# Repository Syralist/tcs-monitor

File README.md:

# tcs-monitor
ein Bus-Monitor für TCS Klingelanlagen

# credits
Version3 basiert auf https://github.com/atc1441/TCSintercomArduino

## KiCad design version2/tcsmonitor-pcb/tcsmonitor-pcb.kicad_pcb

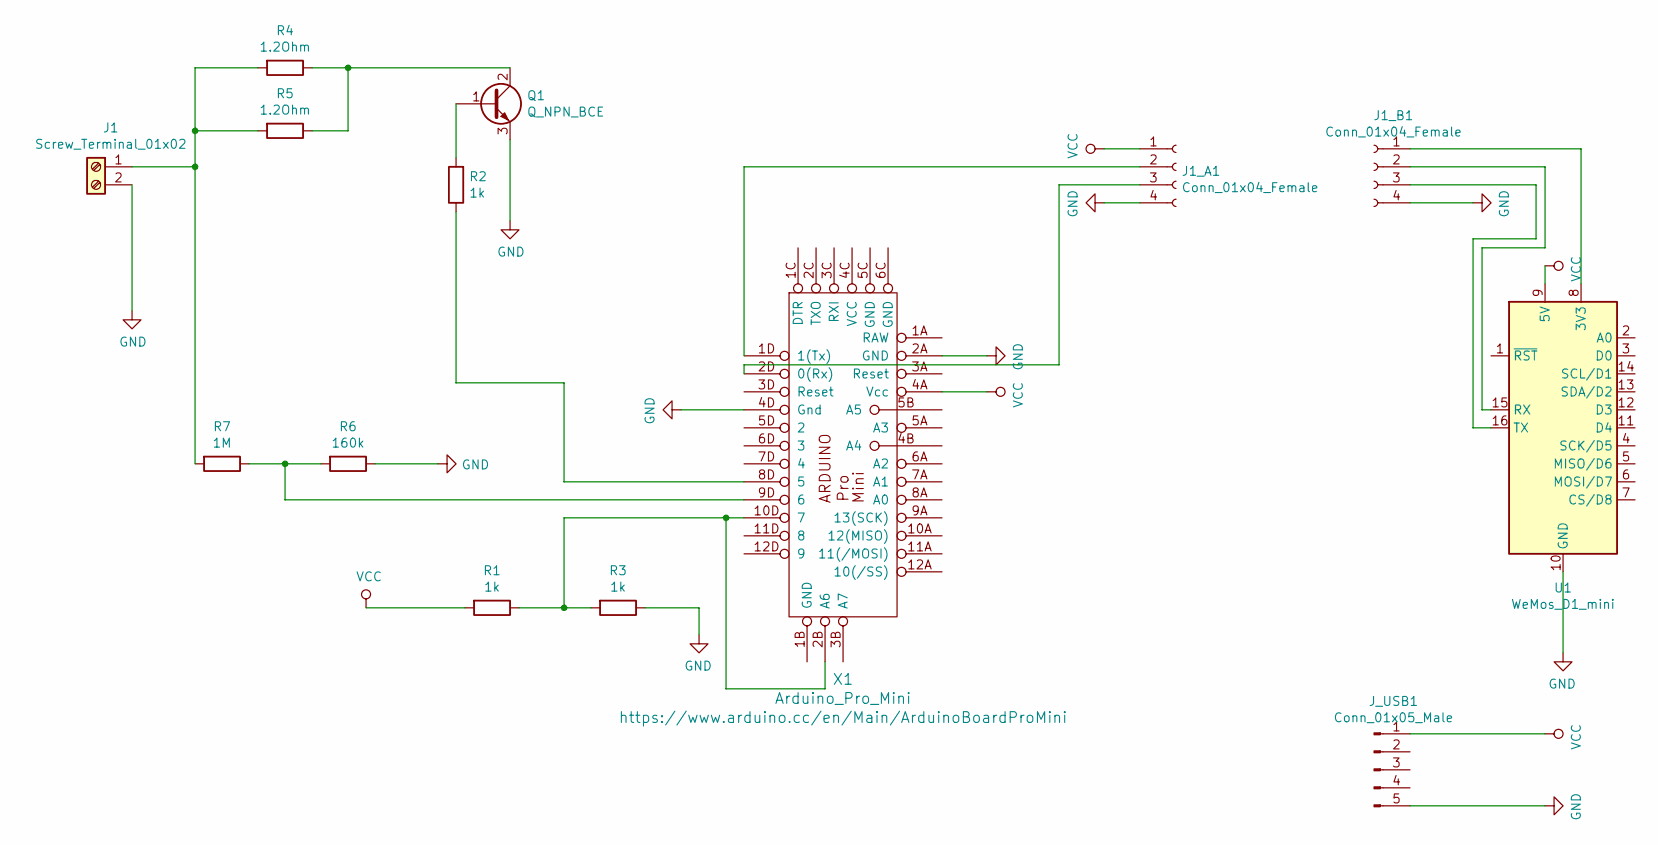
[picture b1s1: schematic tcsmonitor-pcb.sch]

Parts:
J1: Screw_Terminal_01x02; TerminalBlock_bornier-2_P5.08mm
J1_A1, J1_B1: Conn_01x04_Female; PinHeader_1x04_P2.54mm_Vertical
J_USB1: Conn_01x05_Male; PinHeader_1x05_P2.54mm_Vertical
Q1: Q_NPN_BCE; TO-3P-3_Vertical
R1, R2, R3: 1k; R_Axial_DIN0207_L6.3mm_D2.5mm_P7.62mm_Horizontal
R4, R5: 1.2Ohm; R_Axial_DIN0207_L6.3mm_D2.5mm_P7.62mm_Horizontal
R6: 160k; R_Axial_DIN0207_L6.3mm_D2.5mm_P7.62mm_Horizontal
R7: 1M; R_Axial_DIN0207_L6.3mm_D2.5mm_P7.62mm_Horizontal
U1: WeMos_D1_mini; WEMOS_D1_mini_light
X1: Arduino_Pro_Mini

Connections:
GND: J1.2, J1_A1.4, J1_B1.4, J_USB1.5, Q1.3 (E), R3.1, R6.1, U1.10 (GND), X1.2A (GND), X1.4D (Gnd)
unnamed: J1.1, R4.2, R5.2, R7.2
unnamed: J1_A1.2, X1.1D (1(Tx))
unnamed: J1_A1.3, X1.2D (0(Rx))
unnamed: J1_B1.1, U1.8 (3V3)
unnamed: J1_B1.2, U1.15 (RX)
unnamed: J1_B1.3, U1.16 (TX)
unnamed: Q1.1 (B), R2.2
unnamed: Q1.2 (C), R4.1, R5.1
unnamed: R1.1, R3.2, X1.2B (A6), X1.10D (7)
unnamed: R2.1, X1.8D (5)
unnamed: R6.2, R7.1, X1.9D (6)
VCC: J1_A1.1, J_USB1.1, R1.2, U1.9 (5V), X1.4A (Vcc)

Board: 2 copper layers, 14 parts (2 on the bottom side), 13 nets, no tracks yet.

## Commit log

2019-05-30 erste Version des Codes
2019-05-30 Gehäuse hinzugefügt
2019-05-31 erster funktionierender Code.
2019-06-11 größeres Loch für USB Kabel, Löcher für Schrauben
2019-10-04 Schaltplan hinzugefügt
2019-12-28 schematic vorbereitet
2020-01-26 gitignore hinzugefügt
2020-01-26 minor changes
2020-02-01 bak-Dateien gelöscht. Connectoren eingefügt.
2020-02-28 Code angepasst an ArduinoJson V6.
2020-09-23 neues PCB
2020-09-23 Version mit Interrupt auf ESP8266 und MQTT
2020-09-24 OTA hinzugefügt
2020-09-24 auto discovery info für HomeAssistant hinzugefügt
2020-09-24 Payload angepasst und Config ergänzt
